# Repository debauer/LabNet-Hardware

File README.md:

# LabNet Hardware

#LabNet-canable

a fork of canable  
Easy access the LabNet from any PC and integrate Raspberry PIs and Beaglebones in the Infrastructure.

# Nodes Generation 2

### Power-Hub

David, Fablab KA, www.debauer.net

- 4x USB mit 5V und 5A
- 8x RJ45 LabNet (2x CA, 24V)
- 2x RJ45 LabNet Passtrouth (2x CAN, no Power)
- 1x RJ45 Rittal Steckdosenleisten (RS485, 24V)
- 8x Schmelzsicherung (2A) für Verbrauchergruppen
- 1Wire DS18x20 (Temperatur)
- LabNet Node (Sicherungsstatus, RS485, 1Wire Temperatur)

### Basis

David, Fablab KA, www.debauer.net

- 5V 5A DCDC
- Arduino Pro Mini
- CAN Controller
- 1x RJ45 Rittal Steckdosenleisten (RS485, 24V)
- 2x RJ45 LabNet passthru (2x CAN, no Power)
- 1Wire DS18x20 (Temperatur)
- Addon Buchsen (~80% Arduino Pinning, aber nicht Mechanisch Kompatibel)

### Basis Addon HR20

David, Fablab KA, www.debauer.net

- 1,44" LCD 128x128px SPI
- 3 Buttons
- 1:1 10 Pol Wannenstecker für HR20 Heizungsregler

### Basis Addon RGBW

David, Fablab KA, www.debauer.net

- 4x Mosfet
- i2c PWM Treiber

# Obsolote Nodes Generation 1

### iomodul V2.0 10'14
Obsolete + working Prototypes @ FabLab KA

Sarah, Fablab KA  
Florolf, Entropia KA  

### iomodul V2.1 03'15 mod 

Obsolete + no Prototype

David Bauer, FabLab KA

- Hühnerfutter size changed from 0604 to 0805
- added and moved the LEDs
- changed JTAG/SWD connector layout to fit ti the STM SWD

### iomodul V3.0 06'15 swap ARM Chip

Obsolete + no Prototype

- Changed ARM from STM M0 to ATMEL SAM D21 (ARM M0)
- added USB

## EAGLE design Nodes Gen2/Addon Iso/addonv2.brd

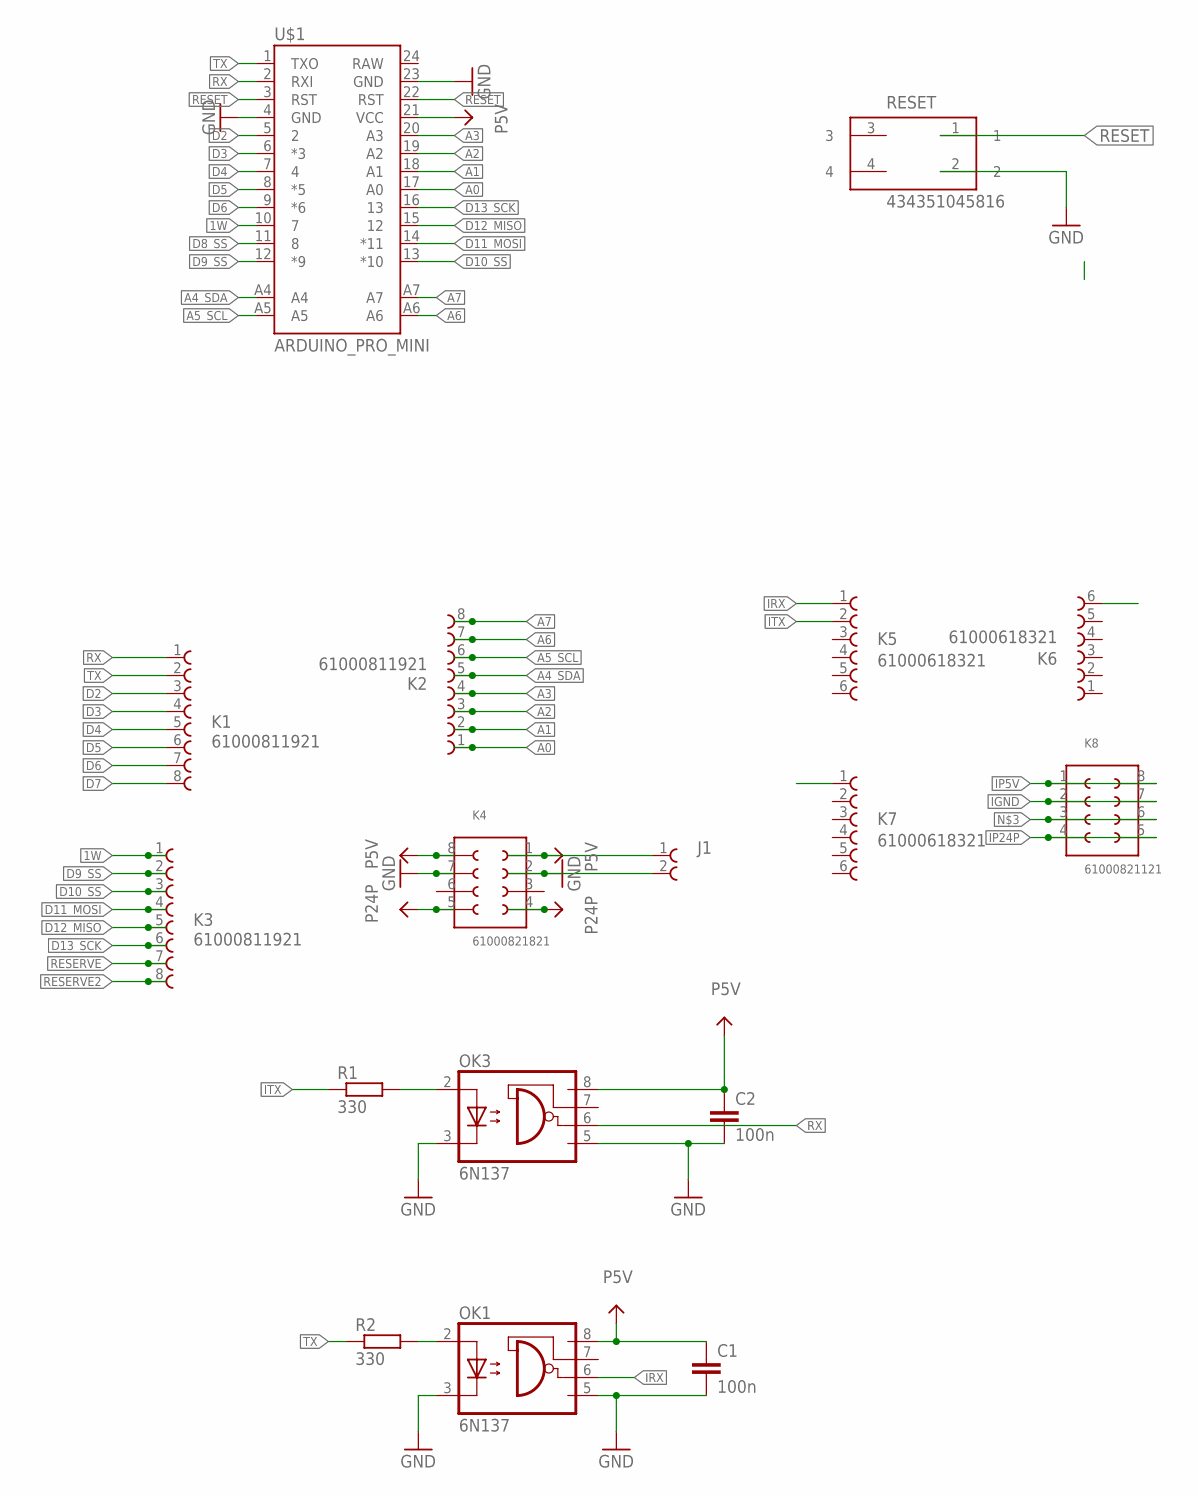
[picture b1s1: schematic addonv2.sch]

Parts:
C1, C2: 100n; C0805
J1: 691322310002
K1, K2, K3: 61000811921
K4: 61000821821
K5, K6, K7: 61000618321
K8: 61000821121
OK1, OK3: 6N137; DIL08
R1, R2: 330; R0805
RESET: 434351045816
U$1: ARDUINO_PRO_MINI

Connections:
1W: K3.1, U$1.10 (7)
A0: K2.1, U$1.17 (A0)
A1: K2.2, U$1.18 (A1)
A2: K2.3, U$1.19 (A2)
A3: K2.4, U$1.20 (A3)
A4_SDA: K2.5, U$1.A4
A5_SCL: K2.6, U$1.A5
A6: K2.7, U$1.A6
A7: K2.8, U$1.A7
D2: K1.3, U$1.5 (2)
D3: K1.4, U$1.6 (*3)
D4: K1.5, U$1.7 (4)
D5: K1.6, U$1.8 (*5)
D6: K1.7, U$1.9 (*6)
D7: K1.8
D8_SS: U$1.11 (8)
D9_SS: K3.2, U$1.12 (*9)
D10_SS: K3.3, U$1.13 (*10)
D11_MOSI: K3.4, U$1.14 (*11)
D12_MISO: K3.5, U$1.15 (12)
D13_SCK: K3.6, U$1.16 (13)
GND: C1.2, C2.2, J1.2, K4.2, K4.7, OK1.3 (C), OK1.5 (GND), OK3.3 (C), OK3.5 (GND), RESET.2, U$1.4 (GND), U$1.23 (GND)
IGND: K8.2, K8.7
IP5V: K8.1, K8.8
IP24P: K8.4, K8.5
IRX: K5.1, OK1.6 (VO)
ITX: K5.2, R1.1
unnamed: K8.3, K8.6
unnamed: OK3.2 (A), R1.2
unnamed: OK1.2 (A), R2.2
P5V: C1.1, C2.1, J1.1, K4.1, K4.8, OK1.8 (VCC), OK3.8 (VCC), U$1.21 (VCC)
P24P: K4.4, K4.5
RESERVE: K3.7
RESERVE2: K3.8
RESET: RESET.1, U$1.3 (RST), U$1.22 (RST)
RX: K1.1, OK3.6 (VO), U$1.2 (RXI)
TX: K1.2, R2.1, U$1.1 (TXO)

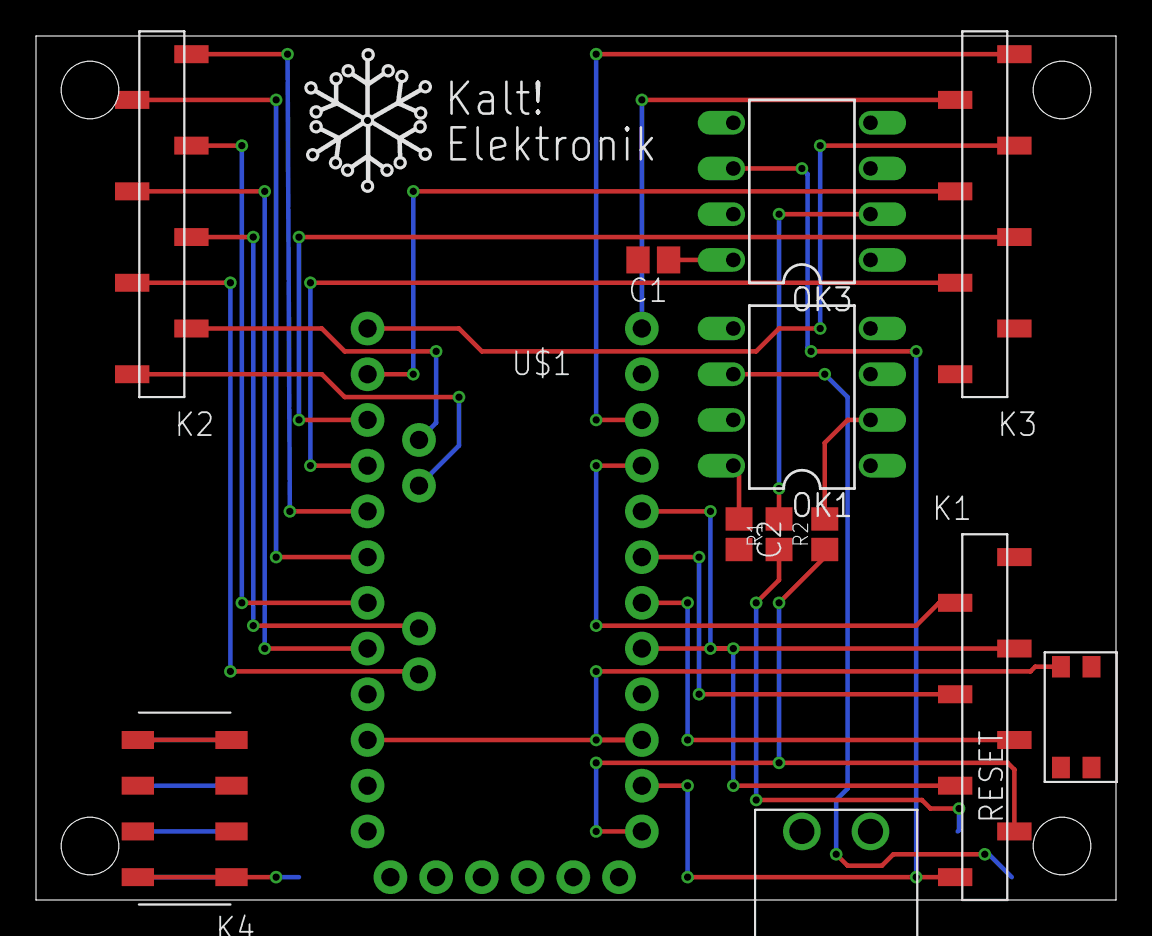
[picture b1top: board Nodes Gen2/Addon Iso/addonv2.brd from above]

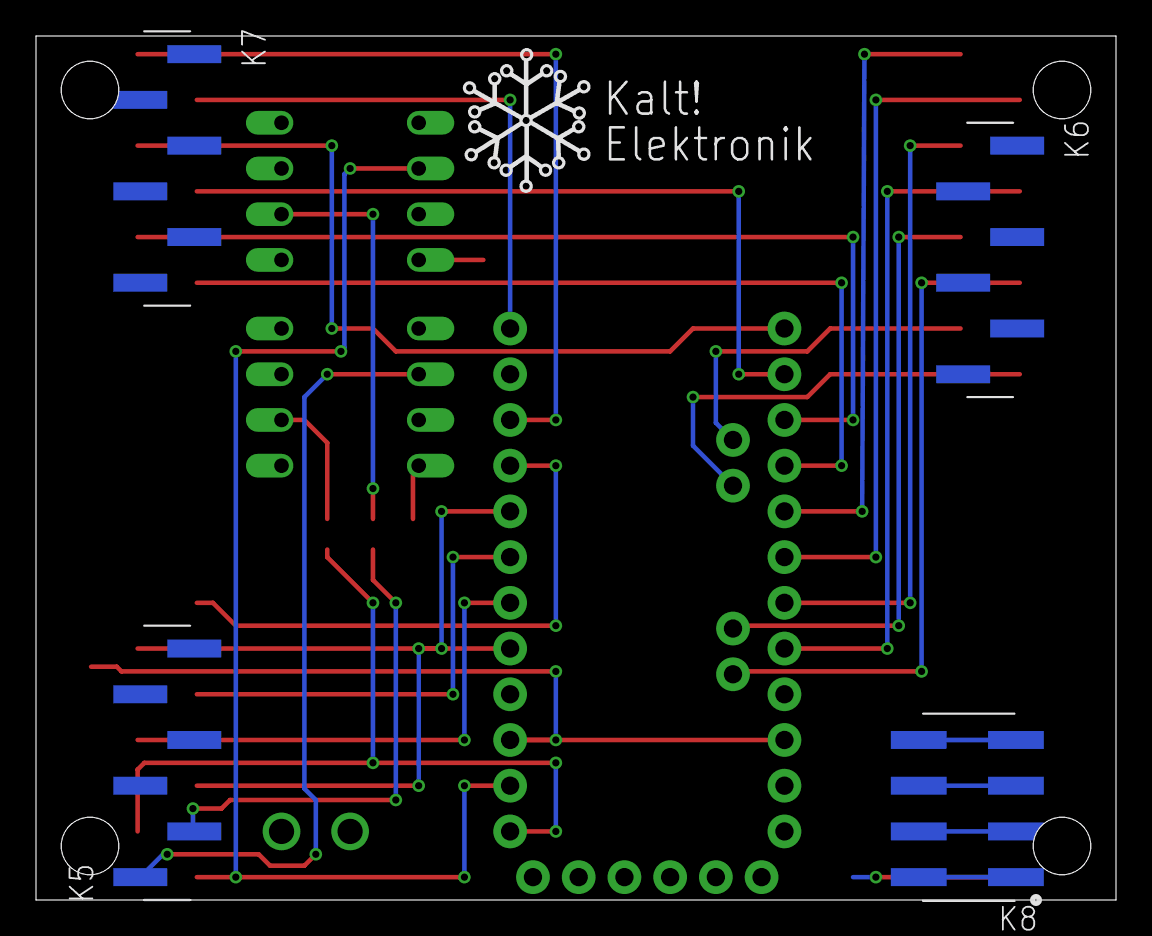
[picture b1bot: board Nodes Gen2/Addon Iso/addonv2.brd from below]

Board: 2 copper layers, 60.0 x 48.0 mm, 19 parts (5 on the bottom side), 33 nets.

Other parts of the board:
U$2, U$3: KALT!ELEKTRONIK

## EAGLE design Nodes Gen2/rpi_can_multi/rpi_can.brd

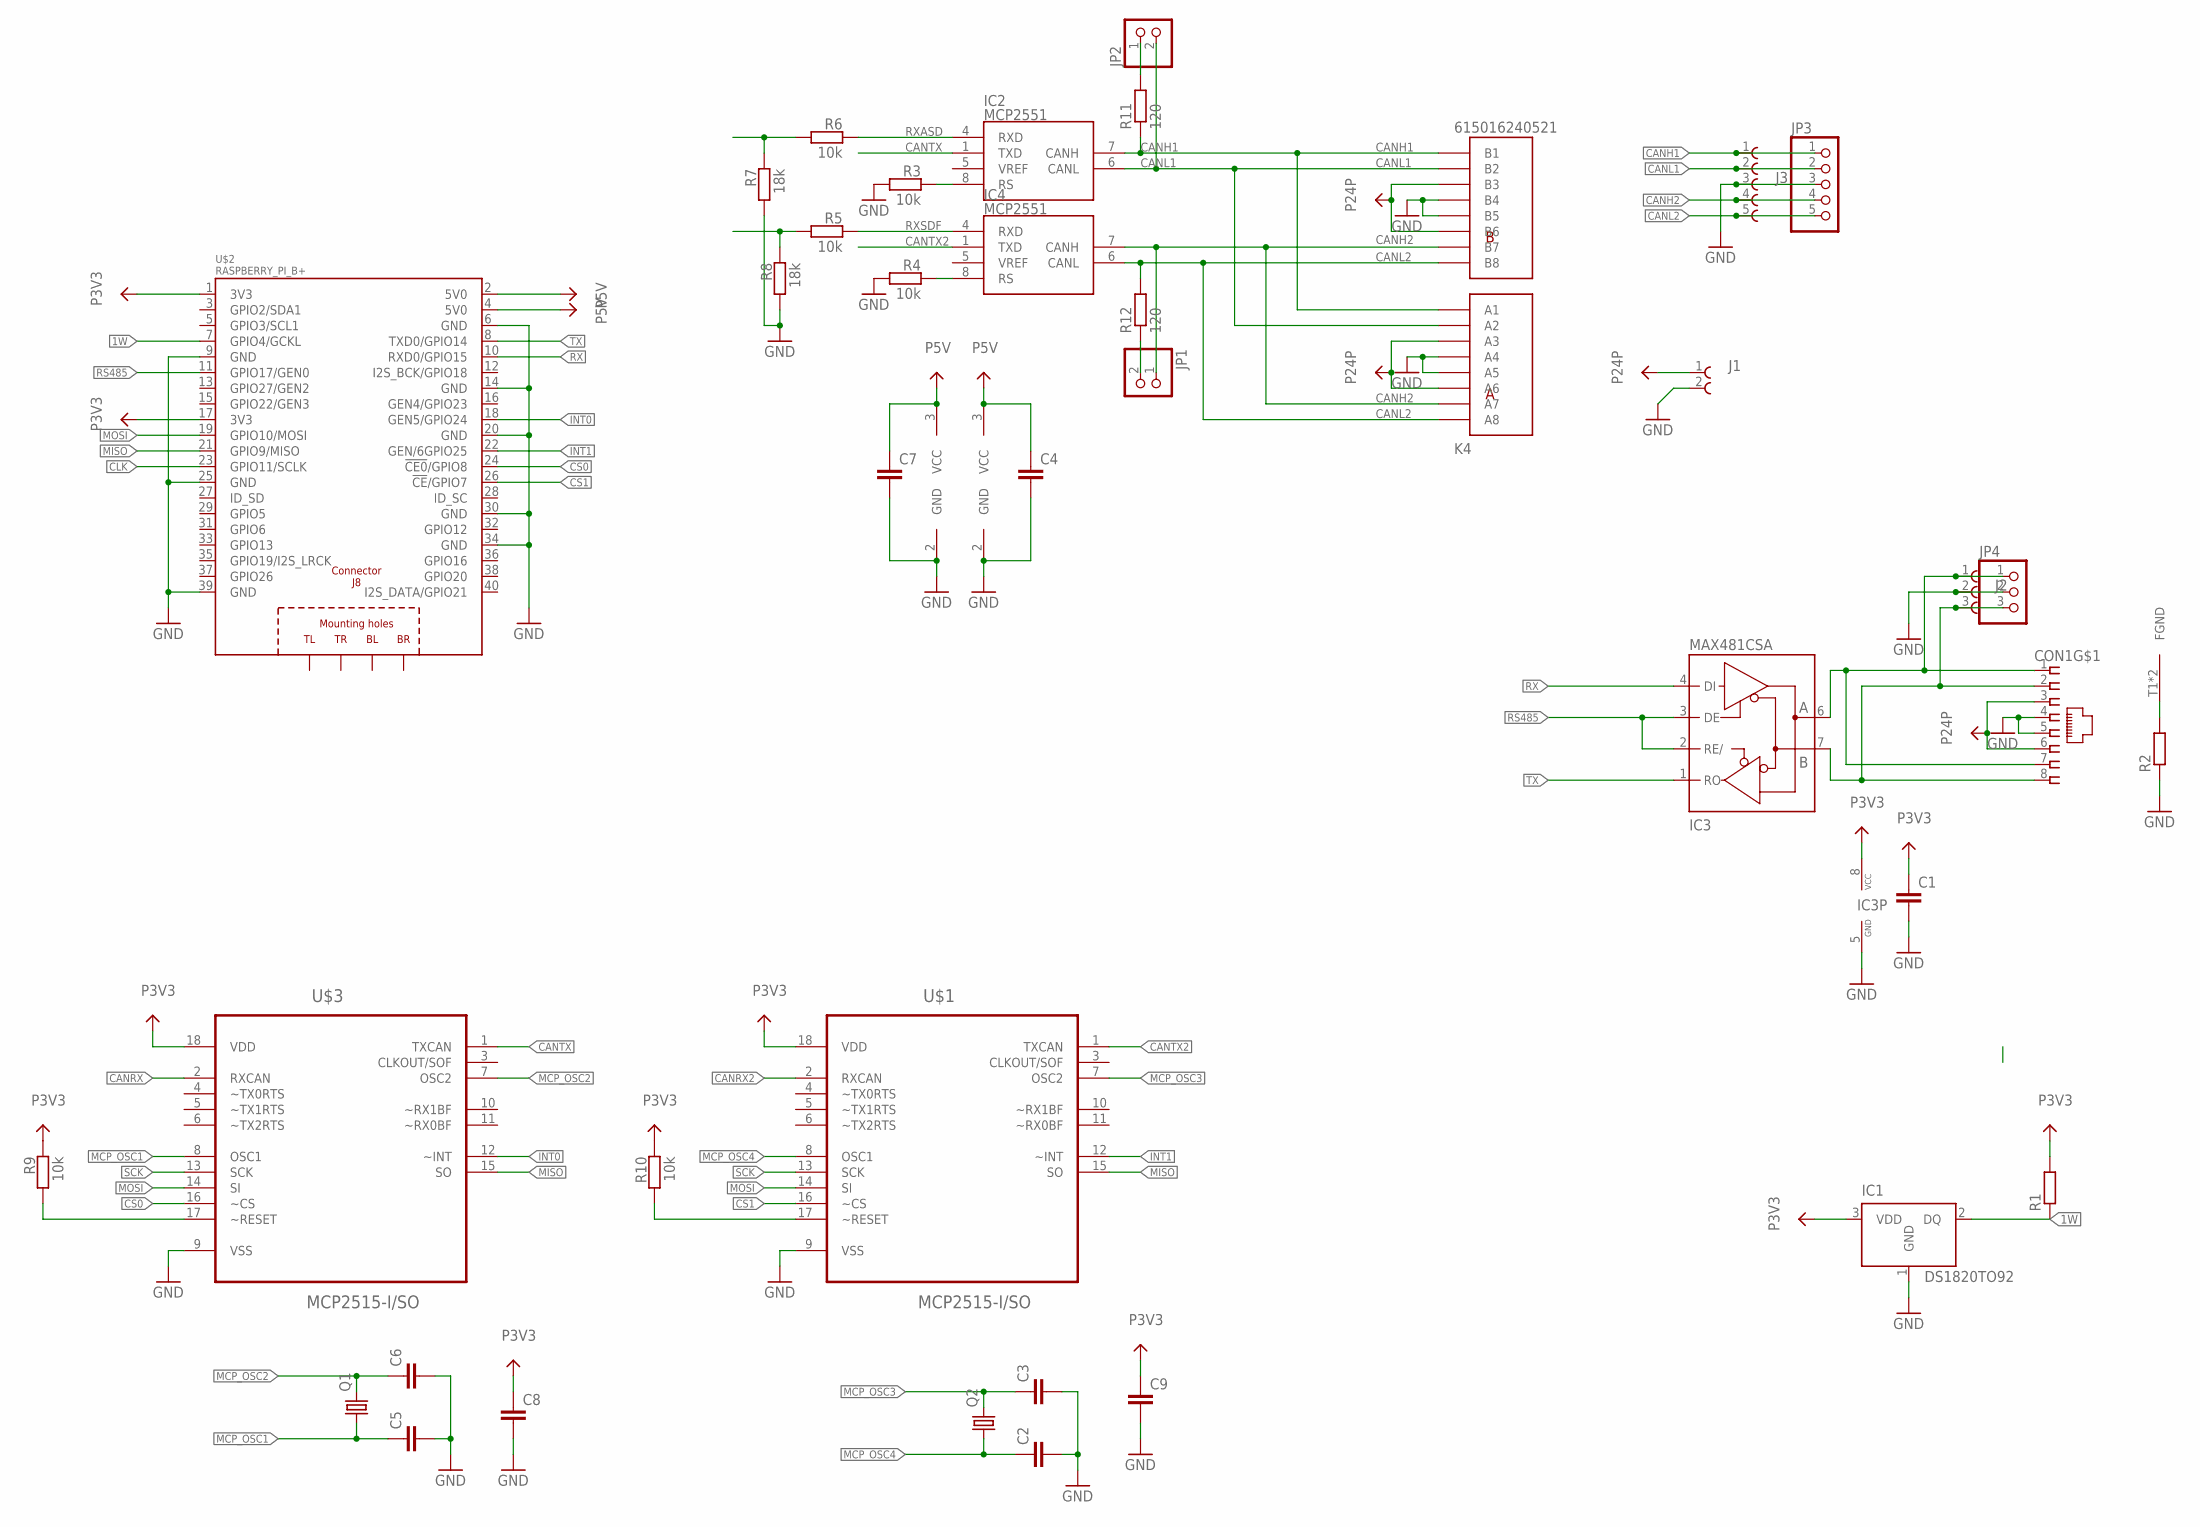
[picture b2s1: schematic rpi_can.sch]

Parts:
C1, C2, C3, C4, C5, C6, C7, C8, C9: C-EUC0805; C0805
CON1: MEBP_8-8G; MEBP
IC1: DS1820TO92; TO-92
IC2, IC4: MCP2551; SO-8
IC3: MAX481CSA; SO08
J1: 691322310002
J2: 691322310003
J3: 691322310005
JP1, JP2: PINHD-1X2; 1X02
JP3: PINHD-1X5; 1X05
JP4: PINHD-1X3; 1X03
K4: 615016240521
Q1, Q2: CRYSTALHC49S; HC49/S
R1, R2: R-EU_R0805; R0805
R3, R4, R5, R6, R9, R10: 10k; R0805
R7, R8: 18k; R0805
R11, R12: 120; R0805
U$1, U$3: MCP2515-I/SO; SOIC127P1034X264-18N
U$2: RASPBERRY_PI_B+

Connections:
1W: IC1.2 (DQ), R1.1, U$2.7 (GPIO4/GCKL)
CANH1: IC2.7 (CANH), J3.1, JP3.1, K4.A1, K4.B1, R11.1
CANH2: IC4.7 (CANH), J3.4, JP1.1, JP3.4, K4.A7, K4.B7
CANL1: IC2.6 (CANL), J3.2, JP2.2, JP3.2, K4.A2, K4.B2
CANL2: IC4.6 (CANL), J3.5, JP3.5, K4.A8, K4.B8, R12.2
CANRX: R6.2, R7.1, U$3.2 (RXCAN)
CANRX2: R5.2, R8.1, U$1.2 (RXCAN)
CANTX: IC2.1 (TXD), U$3.1 (TXCAN)
CANTX2: IC4.1 (TXD), U$1.1 (TXCAN)
CLK: U$2.23 (GPIO11/SCLK)
CS0: U$2.24 (!CE0!/GPIO8), U$3.16 (~CS)
CS1: U$1.16 (~CS), U$2.26 (!CE!/GPIO7)
GND: C1.2, C2.2, C3.2, C4.2, C5.2, C6.2, C7.2, C8.2, C9.2, CON1.4, CON1.5, IC1.1 (GND), IC2.2 (GND), IC3.5 (GND), IC4.2 (GND), J1.2, J2.2, J3.3, JP3.3, JP4.2, K4.A4, K4.A5, K4.B4, K4.B5, R2.1, R3.2, R4.2, R7.2, R8.2, U$1.9 (VSS), U$2.6 (GND), U$2.9 (GND), U$2.14 (GND), U$2.20 (GND), U$2.25 (GND), U$2.30 (GND), U$2.34 (GND), U$2.39 (GND), U$3.9 (VSS)
INT0: U$2.18 (GEN5/GPIO24), U$3.12 (~INT)
INT1: U$1.12 (~INT), U$2.22 (GEN/6GPIO25)
MCP_OSC1: C5.1, Q1.1, U$3.8 (OSC1)
MCP_OSC2: C6.1, Q1.2, U$3.7 (OSC2)
MCP_OSC3: C3.1, Q2.2, U$1.7 (OSC2)
MCP_OSC4: C2.1, Q2.1, U$1.8 (OSC1)
MISO: U$1.15 (SO), U$2.21 (GPIO9/MISO), U$3.15 (SO)
MOSI: U$1.14 (SI), U$2.19 (GPIO10/MOSI), U$3.14 (SI)
unnamed: R10.2, U$1.17 (~RESET)
unnamed: IC2.8 (RS), R3.1
unnamed: CON1.T1 (FGND), CON1.T2 (FGND), R2.2
unnamed: IC4.8 (RS), R4.1
unnamed: R9.2, U$3.17 (~RESET)
unnamed: JP2.1, R11.2
unnamed: JP1.2, R12.1
P3V3: C1.1, C8.1, C9.1, IC1.3 (VDD), IC3.8 (VCC), R1.2, R9.1, R10.1, U$1.18 (VDD), U$2.1 (3V3), U$2.17 (3V3), U$3.18 (VDD)
P5V: C4.1, C7.1, IC2.3 (VCC), IC4.3 (VCC), U$2.2 (5V0), U$2.4 (5V0)
P24P: CON1.3, CON1.6, J1.1, K4.A3, K4.A6, K4.B3, K4.B6
RS485: IC3.2 (RE/), IC3.3 (DE), U$2.11 (GPIO17/GEN0)
RS485_A: CON1.1, CON1.7, IC3.6 (A), J2.1, JP4.1
RS485_B: CON1.2, CON1.8, IC3.7 (B), J2.3, JP4.3
RX: IC3.4 (DI), U$2.10 (RXD0/GPIO15)
RXASD: IC2.4 (RXD), R6.1
RXSDF: IC4.4 (RXD), R5.1
SCK: U$1.13 (SCK), U$3.13 (SCK)
TX: IC3.1 (RO), U$2.8 (TXD0/GPIO14)

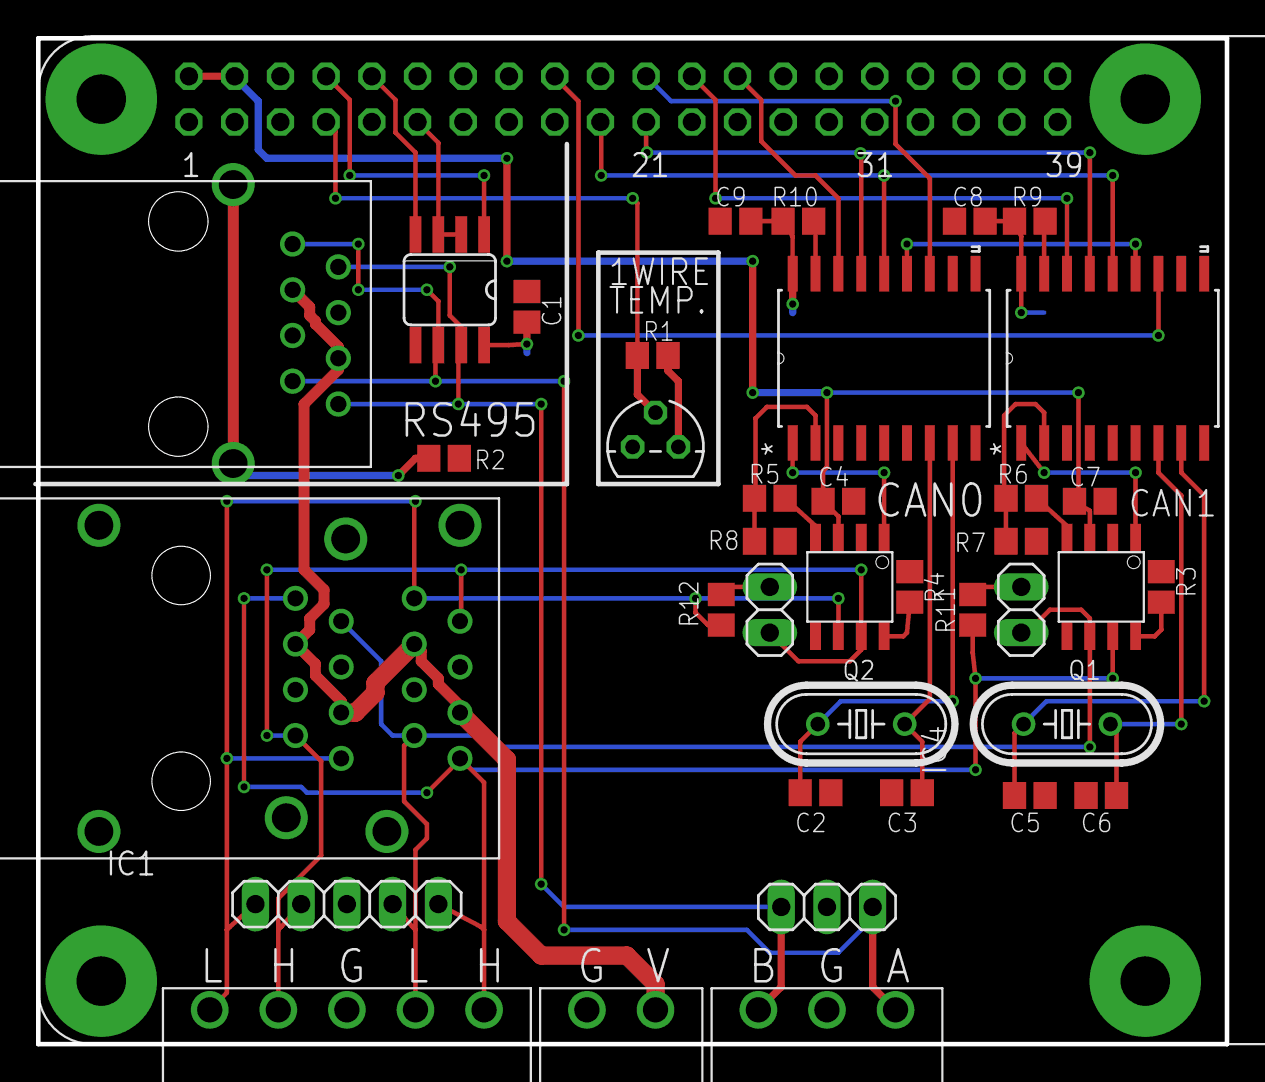
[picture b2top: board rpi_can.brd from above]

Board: 2 copper layers, 66.0 x 55.9 mm, 39 parts (0 on the bottom side), 38 nets.

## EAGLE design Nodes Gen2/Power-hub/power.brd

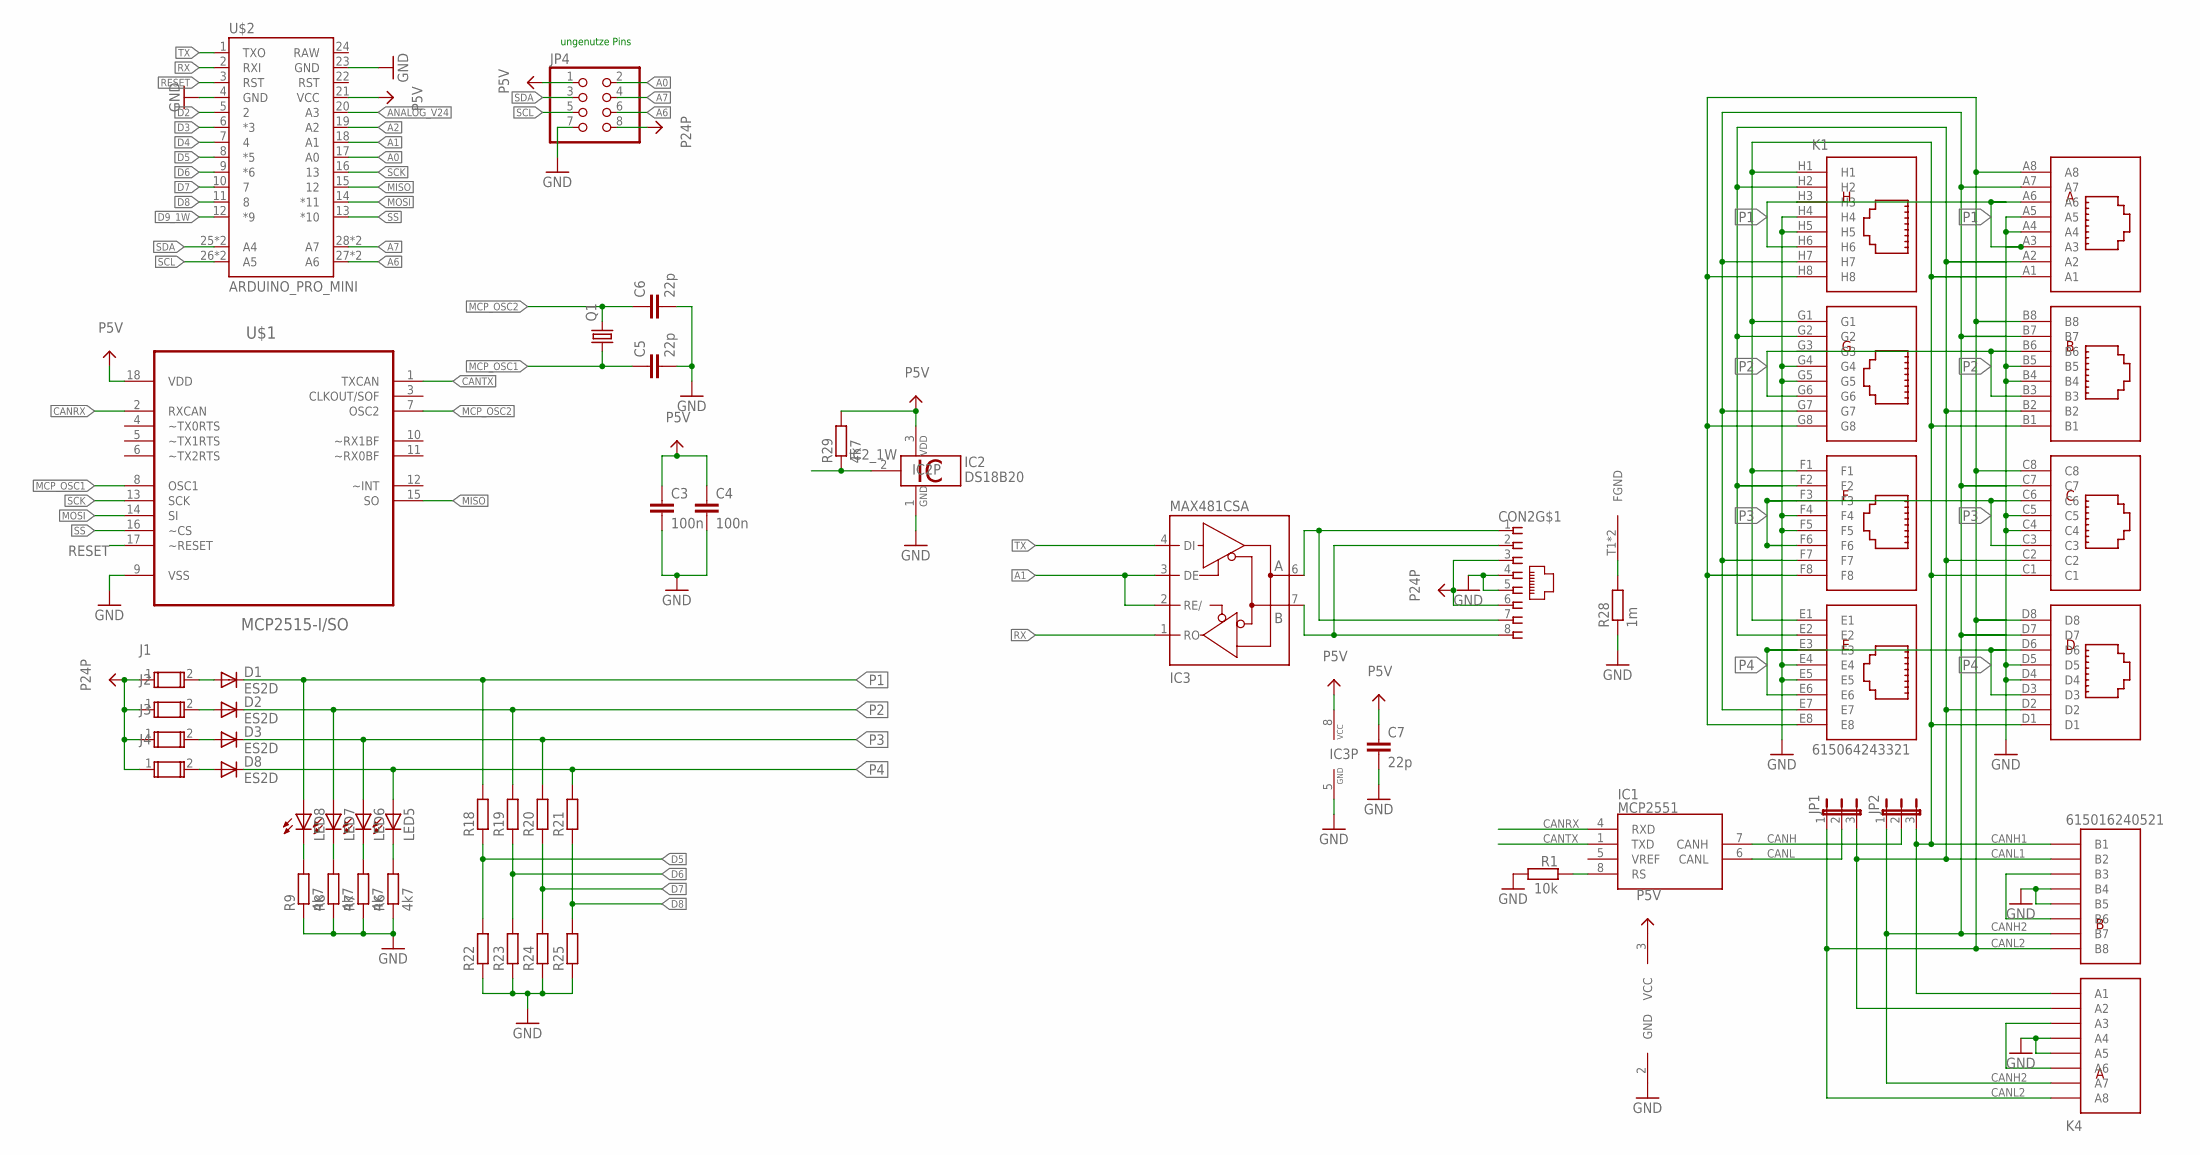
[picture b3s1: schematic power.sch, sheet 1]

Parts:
C3, C4: 100n; C0805
C5, C6, C7: 22p; C0805
CON2: MEBP_8-8G; MEBP
D1, D2, D3, D8: ES2D; SMB
IC1: MCP2551; SO-8
IC2: DS18B20; TO92-
IC3: MAX481CSA; SO08
J1, J2, J3, J4: 696101000002
JP1, JP2: JP2E; JP2
JP4: PINHD-2X4; 2X04
K1: 615064243321
K4: 615016240521
LED5, LED6, LED7, LED8: LED3MM
Q1: CRYSTALHC49S; HC49/S
R1: 10k; R0603
R6, R7, R8, R9, R29: 4k7; R0805
R18, R19, R20, R21, R22, R23, R24, R25: R-EU_R0805; R0805
R28: 1m; R0805
U$1: MCP2515-I/SO; SOIC127P1034X264-18N
U$2: ARDUINO_PRO_MINI

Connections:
A0: JP4.2, U$2.17 (A0)
A1: IC3.2 (RE/), IC3.3 (DE), U$2.18 (A1)
A2: U$2.19 (A2); also elsewhere on the board
A6: JP4.6, U$2.27 (A6), U$2.A6
A7: JP4.4, U$2.28 (A7), U$2.A7
ANALOG_V24: U$2.20 (A3); also elsewhere on the board
CANH: IC1.7 (CANH), JP2.2
CANH1: JP2.3, K1.A1, K1.B1, K1.C1, K1.D1, K1.E1, K1.F1, K1.G1, K1.H1, K4.A1, K4.B1
CANH2: JP2.1, K1.A7, K1.B7, K1.C7, K1.D7, K1.E7, K1.F7, K1.G7, K1.H7, K4.A7, K4.B7
CANL: IC1.6 (CANL), JP1.2
CANL1: JP1.3, K1.A2, K1.B2, K1.C2, K1.D2, K1.E2, K1.F2, K1.G2, K1.H2, K4.A2, K4.B2
CANL2: JP1.1, K1.A8, K1.B8, K1.C8, K1.D8, K1.E8, K1.F8, K1.G8, K1.H8, K4.A8, K4.B8
CANRX: IC1.4 (RXD), U$1.2 (RXCAN)
CANTX: IC1.1 (TXD), U$1.1 (TXCAN)
D2: U$2.5 (2); also elsewhere on the board
D3: U$2.6 (*3); also elsewhere on the board
D4: U$2.7 (4); also elsewhere on the board
D5: R18.1, R22.2, U$2.8 (*5)
D6: R19.1, R23.2, U$2.9 (*6)
D7: R20.1, R24.2, U$2.10 (7)
D8: R21.1, R25.2, U$2.11 (8)
D9_1W: IC2.2 (1W), R29.1, U$2.12 (*9)
GND: C3.2, C4.2, C5.2, C6.2, C7.2, CON2.4, CON2.5, IC1.2 (GND), IC2.1 (GND), IC3.5 (GND), JP4.7, K1.A4, K1.A5, K1.B4, K1.B5, K1.C4, K1.C5, K1.D4, K1.D5, K1.E4, K1.E5, K1.F4, K1.F5, K1.G4, K1.G5, K1.H4, K1.H5, K4.A4, K4.A5, K4.B4, K4.B5, R1.2, R6.1, R7.1, R8.1, R9.1, R22.1, R23.1, R24.1, R25.1, R28.1, U$1.9 (VSS), U$2.4 (GND), U$2.23 (GND); also elsewhere on the board
MCP_OSC1: C5.1, Q1.1, U$1.8 (OSC1)
MCP_OSC2: C6.1, Q1.2, U$1.7 (OSC2)
MISO: U$1.15 (SO), U$2.15 (12)
MOSI: U$1.14 (SI), U$2.14 (*11)
unnamed: IC1.8 (RS), R1.1
unnamed: K4.B3, K4.B6
unnamed: CON2.T1 (FGND), CON2.T2 (FGND), R28.2
unnamed: D1.A, J1.2
unnamed: K4.A3, K4.A6
unnamed: D2.A, J2.2
unnamed: D3.A, J3.2
unnamed: LED5.K (C), R6.2
unnamed: LED6.K (C), R7.2
unnamed: D8.A, J4.2
unnamed: LED7.K (C), R8.2
unnamed: LED8.K (C), R9.2
P1: D1.C, K1.A3, K1.A6, K1.H3, K1.H6, LED8.A, R18.2
P2: D2.C, K1.B3, K1.B6, K1.G3, K1.G6, LED7.A, R19.2
P3: D3.C, K1.C3, K1.C6, K1.F3, K1.F6, LED6.A, R20.2
P4: D8.C, K1.D3, K1.D6, K1.E3, K1.E6, LED5.A, R21.2
P5V: C3.1, C4.1, C7.1, IC1.3 (VCC), IC2.3 (VDD), IC3.8 (VCC), JP4.1, R29.2, U$1.18 (VDD), U$2.21 (VCC); also elsewhere on the board
P24P: CON2.3, CON2.6, J1.1, J2.1, J3.1, J4.1, JP4.8; also elsewhere on the board
RESET: U$1.17 (~RESET), U$2.3 (RST)
RS485_A: CON2.1, CON2.7, IC3.6 (A)
RS485_B: CON2.2, CON2.8, IC3.7 (B)
RX: IC3.1 (RO), U$2.2 (RXI)
SCK: U$1.13 (SCK), U$2.16 (13)
SCL: JP4.5, U$2.26 (A5), U$2.A5
SDA: JP4.3, U$2.25 (A4), U$2.A4
SS: U$1.16 (~CS), U$2.13 (*10)
TX: IC3.4 (DI), U$2.1 (TXO)

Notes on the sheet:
ungenutze Pins

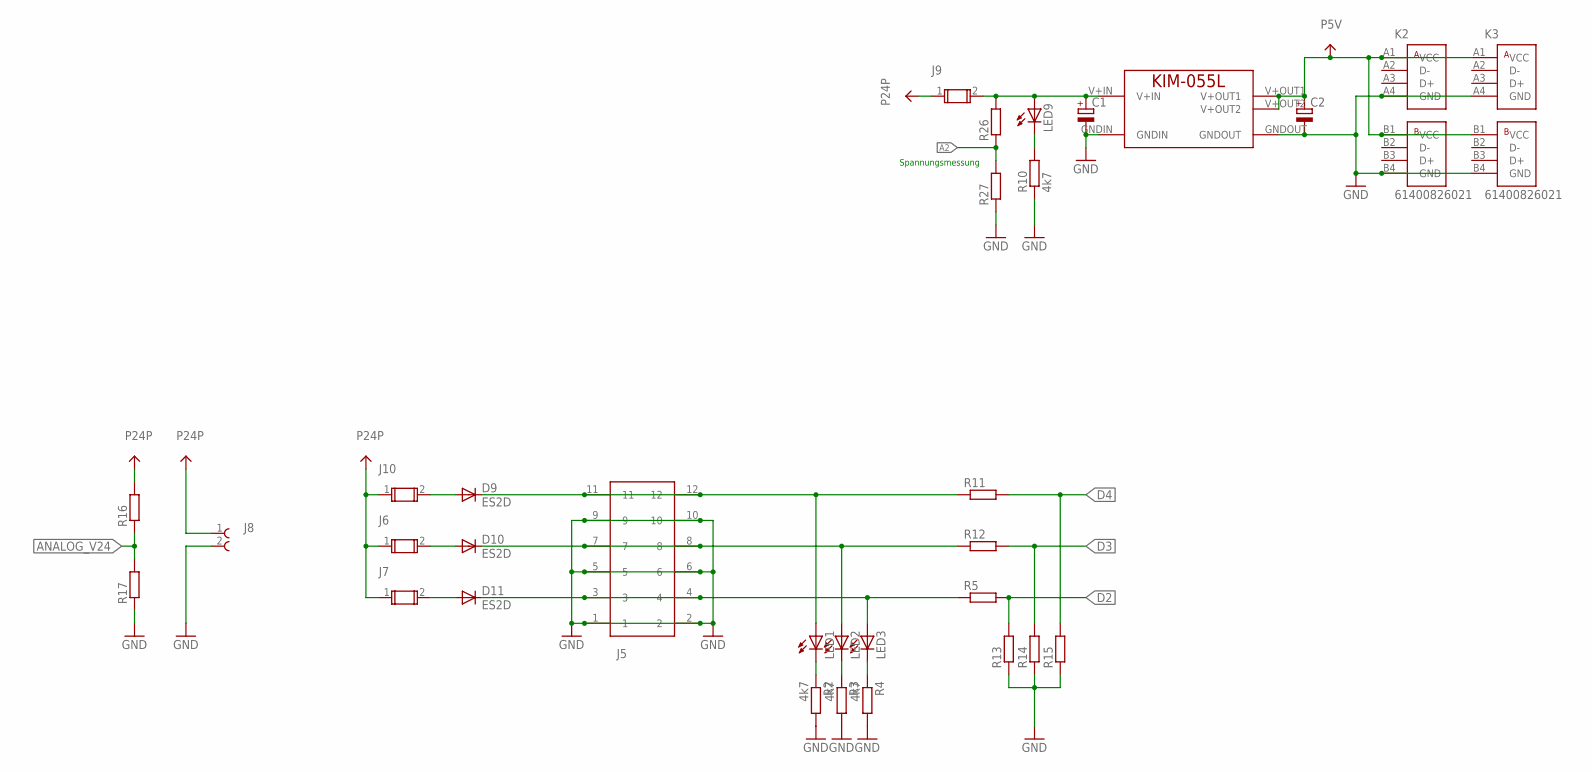
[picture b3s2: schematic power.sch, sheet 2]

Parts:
C1, C2: CPOL-EUE5-10.5; E5-10,5
D9, D10, D11: ES2D; SMB
J5: 691332510012
J6, J7, J9, J10: 696101000002
J8: 691312510002
K2, K3: 61400826021
LED1, LED2, LED3, LED9: LED3MM
MOD1: KIM-055L
R2, R3, R4, R10: 4k7; R0805
R5, R11, R12, R13, R14, R15, R16, R17, R26, R27: R-EU_R0805; R0805

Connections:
A2: R26.1, R27.2; also elsewhere on the board
ANALOG_V24: R16.1, R17.2; also elsewhere on the board
D2: R5.2, R13.2; also elsewhere on the board
D3: R12.2, R14.2; also elsewhere on the board
D4: R11.2, R15.2; also elsewhere on the board
GND: C1.-, C2.-, J5.1, J5.2, J5.5, J5.6, J5.9, J5.10, J8.2, K2.A4 (GND), K2.B4 (GND), K3.A4 (GND), K3.B4 (GND), MOD1.GNDIN, MOD1.GNDOUT, R2.2, R3.2, R4.2, R10.1, R13.1, R14.1, R15.1, R17.1, R27.1; also elsewhere on the board
unnamed: C1.+, J9.2, LED9.A, MOD1.V+IN, R26.2
unnamed: LED9.K (C), R10.2
unnamed: D9.A, J10.2
unnamed: D11.A, J7.2
unnamed: LED1.K (C), R2.1
unnamed: LED2.K (C), R3.1
unnamed: LED3.K (C), R4.1
unnamed: D10.A, J6.2
unnamed: D9.C, J5.11, J5.12, LED1.A, R11.1
unnamed: D10.C, J5.7, J5.8, LED2.A, R12.1
unnamed: D11.C, J5.3, J5.4, LED3.A, R5.1
P5V: C2.+, K2.A1 (VCC), K2.B1 (VCC), K3.A1 (VCC), K3.B1 (VCC), MOD1.V+OUT1, MOD1.V+OUT2; also elsewhere on the board
P24P: J6.1, J7.1, J8.1, J9.1, J10.1, R16.2; also elsewhere on the board

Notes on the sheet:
Spannungsmessung

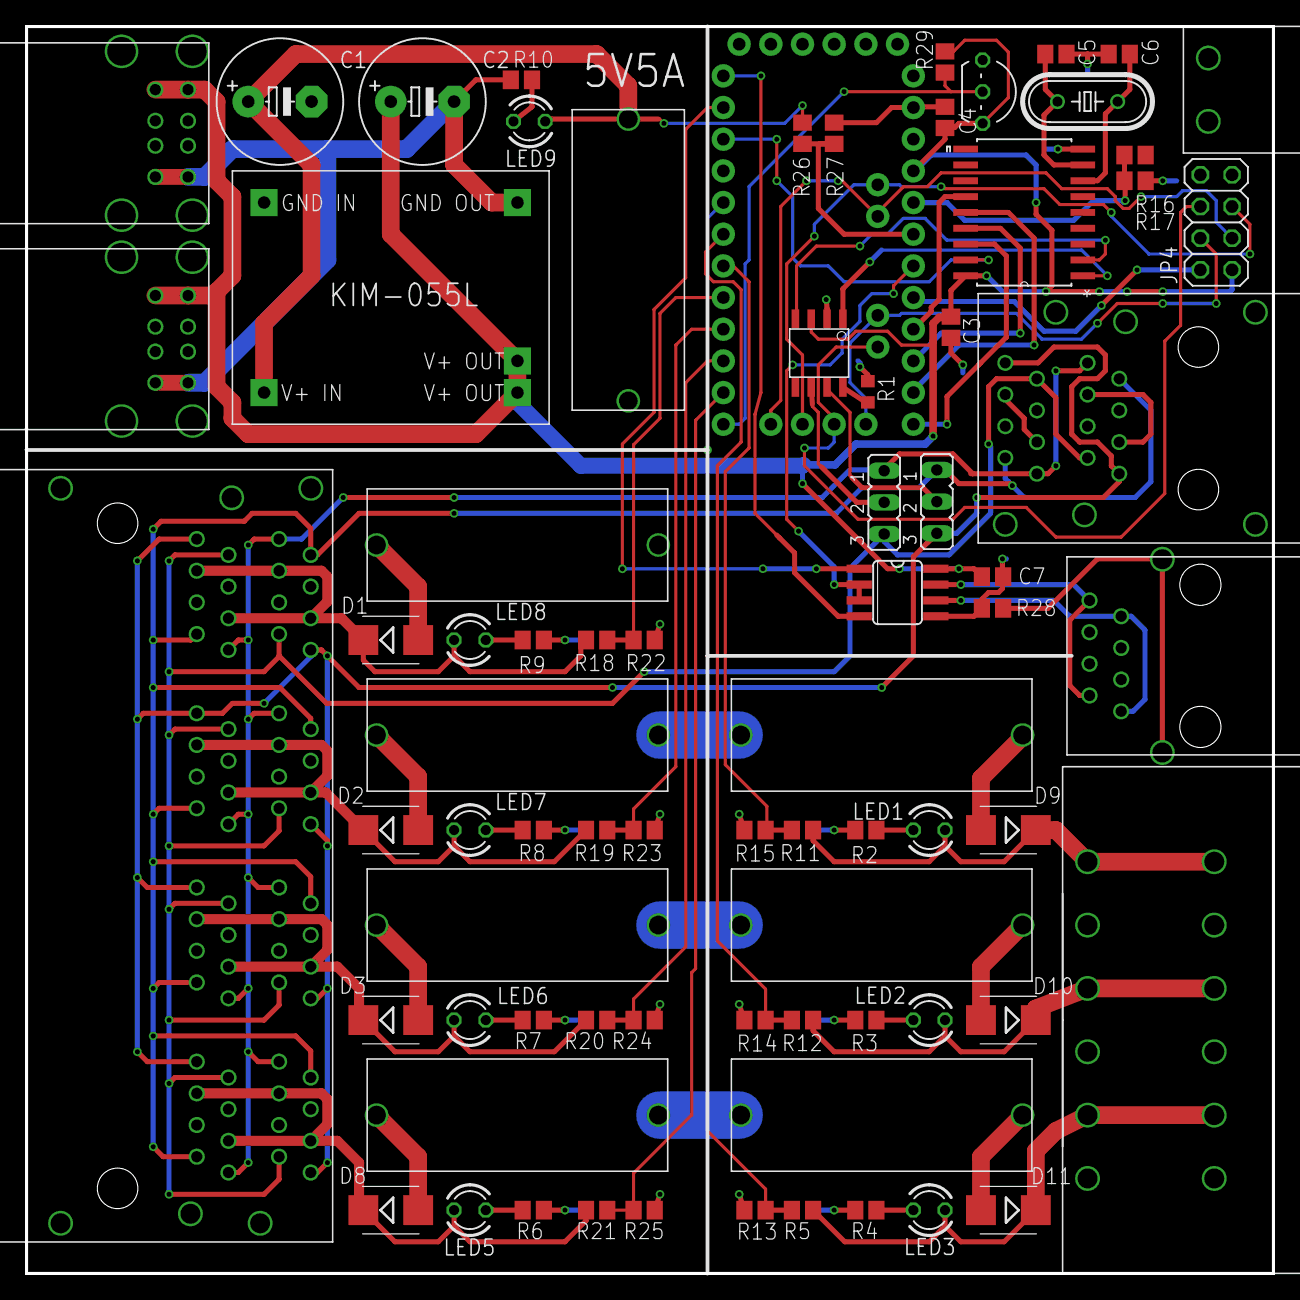
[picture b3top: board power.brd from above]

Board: 2 copper layers, 100.0 x 100.0 mm, 76 parts (0 on the bottom side), 65 nets.

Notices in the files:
parts and their libraries:
Wuerth_TERMINAL_BLOCKS_rev16a: Copyright: Würth Elektronik
SparkFun-Boards: Licensing: Creative Commons ShareAlike 4.0 International - https://creativecommons.org/licenses/by-sa/4.0
